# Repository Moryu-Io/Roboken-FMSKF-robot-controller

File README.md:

# Roboken-FMSKF-robot-controller
## 概要
Teensy4.1を使用した新ROBO-剣出場ロボット[Quinque](https://www.robo-one.com/rankings/view/1127)のHW制御統括マイコンFW  
主な役割は以下
- Ethernet経由Micro-ROSで、ロボット全体を統括する上位LinuxPCと情報をやり取りする
- 5軸ロボットアームへの指示、情報収集
- 4輪メカナムホイールモータの速度制御
- 距離センサを用いて床や相手ロボットの検知を簡易的に行う
- 相手ロボット認識用のカメラをPan/Tiltさせるサーボモータを制御

## SW構成(src内)
すべてFreeRTOSのタスクベースでフォルダ分け

| フォルダ名   | 説明                                                                                            |
| ------------ | ----------------------------------------------------------------------------------------------- |
|RobotManager|Ethernet経由Micro-ROSで、上位のLinuxPCと情報をやり取りしながらHW行動を決定するモジュール|
|ArmDrive|5軸ロボットアームの制御を行う。各関節ごとに[ドライバ](https://github.com/Moryu-Io/Bldc_Servo_Driver_Prj)内で位置/トルク制御を行うため、このモジュールでは指示を統括|
|VehicleDrive|4輪メカナムホイールのモータ制御を行う。こちらはDJIのM2006,C610を使用しており、ドライバ内でのトルク制御を行うため、モータの速度制御から上位の指示/制御を統括|
|FloorDetect|競技エリアから落ちないように距離センサで床面をセンシングするモジュール|
|CameraGimbal|カメラをPan/Tiltさせる汎用サーボモータの制御モジュール|
|Logger|Print文をSDカードに保存するためのDebug用モジュール|
|Debug|DebugPrintやRTOSのリソース状況を出力するDebug用モジュール|
|Utility|汎用モジュール。自作の計算処理など|

## 使用ライブラリ
| フォルダ名   | 説明                                                                                            |
| ------------ | ----------------------------------------------------------------------------------------------- |
|[FreeRTOS-Teensy4](https://github.com/juliandesvignes/FreeRTOS-Teensy4)|RTOS|
|[micro_ros_arduino](https://github.com/micro-ROS/micro_ros_arduino)|Micro-ROS Quinque用のカスタムメッセージを含めてビルドしたものを同梱|
|[IcsClass_V210](https://kondo-robot.com/faq/ics-library-a2)|一部使用している近藤科学製サーボモータ制御用|
|[TsyDMASPI](https://github.com/hideakitai/TsyDMASPI)|IMU用SPIだが現状ほぼ未使用|

# 雑多なメモ
## 新規Msgの追加方法
### msgファイルの作成

`micro_ros_arduino\extras\library_generation\extra_packages`直下にmsgフォルダを作る

[公式チュートリアル](https://micro.ros.org/docs/tutorials/advanced/create_new_type/)に従って、.msgファイルの作成とCMakeLists.txtへの登録を行う

ここには記載がないが、package.xml末尾に以下を追加する必要もある
```
  <build_depend>rosidl_default_generators</build_depend>
  <exec_depend>rosidl_default_runtime</exec_depend>
  <member_of_group>rosidl_interface_packages</member_of_group>
```

### micro_ros_arduinoライブラリを作成する
wsl2にて以下のコマンドを発行
```
sudo service docker start

docker pull microros/micro_ros_static_library_builder:foxy
docker run -it --rm -v $(pwd):/project --env MICROROS_LIBRARY_FOLDER=extras microros/micro_ros_static_library_builder:foxy -p teensy4
```
※2022/05/08 wsl2で上記コマンドでdocker使用時に名前解決ができなくなっていた。原因不明。

[このサイト](https://qiita.com/takkeybook/items/37af683bfb1a4eca6aa2)に従って、`/etc/resolv.conf`に記載のDNSサーバーを変更する

### PC側での準備
通信するPC側では同様のmsg定義フォルダを作成
```
colcon build --symlink-install --packages-up-to interfaces
. install/local_setup.bash
ros2 run micro_ros_agent micro_ros_agent udp4 -p 9999
```

### Micro-ROSテスト方法memo
- topic
```
ros2 topic echo /VehicleInfo
```

- service
```
ros2 service call /ProcStatus interfaces/srv/ProcStatus "{id: 1}"
```

## FreeRTOSの初期化修正とFault診断

2026-11-01、初回INITでの再起動を引き起こしていたMSP初期化を修正した。
TeensyduinoのRAMベクタテーブルはslot 0も`unused_interrupt_vector`で埋められる。
従来のFreeRTOSポートは`VTOR → vector[0]`を初期MSPとしていたため、割り込みの
スタック保存がITCM内の`pinMode()`等を上書きしていた。
`prvPortStartFirstTask()`はTeensyのResetHandlerと同じ`_estack`を直接ロードする。
修正後、ユーザーの実機試験で症状が解消したとの報告あり。

RT1062のNVIC優先度も実装に合わせて4bitとし、syscall maskを`0x20`、
kernel priorityを`0xF0`に修正済み。これらの修正は診断defineに依存せず常時有効。
回帰チェックは `python3 test/check_rtos_priorities.py` と、build後の
`python3 test/check_rtos_msp.py`（生成命令で`_estack`のロードを確認）。

再利用するFault診断は `src/Debug/fault_trace.hpp` のdefineで切り替える。
既定はすべて無効。通常ビルドには独自Faultハンドラ・保存RAM・起動診断ログ・
MPU設定変更を含めない。Teensy core標準のFault処理は維持する。

| build flag | 機能 | 既定値 |
| --- | --- | --- |
| `-D ENABLE_FAULT_DIAGNOSTICS=1` | PSP/MSPに対応したFault記録、レジスタ・命令列保存、起動時表示 | `0` |
| `-D ENABLE_ITCM_WRITE_GUARD=1` | 診断有効時、MPUで命令RAMへのCPU書き込みを捕捉 | `0` |

PlatformIOの既存`build_flags`へ必要なflagを追記して使う。ITCM保護には両方を指定する。
ソフトウェアbreakpoint等で実行中のコードを書き換える場合、ITCM保護は無効にする。

診断有効時はUSBシリアル接続後に`[BOOT]`、`[RTOS]`、前回の`[FAULT]` / `CrashReport`を表示する。
接続待ちで起動を止めない。位置特定には`[FAULT] stacked PC`を使う。
core標準のCrashReportはMSP固定なので、FreeRTOSタスクのPCと異なる場合がある。
Fault時のPC周辺64 bytesをFlash内の元コードと比較し、`[CODE]`で出力する。
不正なstackやコード範囲は参照しない。記録はリセットで消えないRAMに識別値・checksum付きで保存する。
既存のカスタムFaultハンドラは置き換えず、標準の報告・自動再起動処理へ戻す。
再起動だけではWatchdogと断定せず、リセット要因とFault種別を確認する。

調査時は実機へ書き込んだ`firmware.elf`とログを対で保存する。再buildするとアドレスが変わる。
記録・範囲チェック・MPU設定保持のホスト検査は `python3 test/check_fault_trace.py`。
GPIO32/34専用のDWT監視、初回INITの段階ログ、旧BASEPRI値の比較検査は撤去した。

micro-ROSは時刻同期に失敗しても購読を維持し、20msの試行を1秒間隔で繰り返す。
同期までは終端イベントをADTの既存16件queueに保持し、同期後に送信する。
接続生成等の長い処理後は周期待ちの基準を更新して、他タスクを圧迫する追い付き実行を避ける。
これらは接続処理の修正として維持する。

## WebUIのマニュアル操作

`Command=12`で専用の手動モードへ入ります。モード切り替え自体は腕の移動やトルクONを行いません。
WebUIは停止指令を先に送り、必要な初期化（4）と構え（1）は別操作にします。
手動では構えの実動作完了後、最初のTimeAngle受信時にPOSITIONING_SEQへ遷移します。
自律開始（2）を送る必要はありません。実行中のTimeAngleと重なる要求は拒否します。

`manual_control/hardware_state`（std_msgs/UInt8）をVehicleInfoと同じ周期で配信します。
0=手動無効、1=手動有効・構え未完了、2=構え完了・打突受付可能、3=打突実行中です。
0（停止・トルクOFF）・2（自律開始）・3（終了）で手動を解除し、1（構え）・4（初期化）では維持します。
走行の床・IMU保護とcmd_velの500 ms watchdogは既存どおりです。

対応するROS側のinterfaces・arm_action_plan・vehicle_action・robot_web_uiと併せて更新してください。
通常の`pio run -e teensy41`でビルドできます。既存のCommandと標準UInt8を使うため、
この変更に伴うmicro_ros_arduinoライブラリの再生成は不要です。書き込みは機体の停止を確認して別途行います。

## FreeRTOS

こちらのリポジトリをベースに、libフォルダに格納
https://github.com/juliandesvignes/FreeRTOS-Teensy4

変更点
* heap3からheap4に
    * heap3はC言語のmallocなどのラッパだが、Teensyduinoではmallocで確保されるのは通常RAM。
    * heap4でucHeapをTCMに配置することで高速性を担保
* 別途configファイルを設定

## アーム実行進捗

`ArmExecutionProgress`（相対topic、reliable）で、`header.stamp`は通知時刻、
`id`はTimeAngle ID、`elapsed_ms`はADTで実際に指令した補間位置、
`status`はRUNNING=0 / COMPLETED=1 / ABORTED=2を送信する。
受信・queue投入時点ではRUNNINGにしない。終端イベントは16件の専用queueに保持し、
RMTタスクから送信する。進行中のsnapshotはcritical sectionで受け渡す。
ArmInfoとProcStatusは引き続き利用できる。

TimeAngleは5軸の点数・各点の時刻が一致する1～32点、時刻は非減少であること。
受信データはADT向けmessageへコピーし、次のROS callbackによる上書きを防ぐ。
不正入力、buffer満杯、POSITIONING_SEQモード外の要求はABORTEDを通知する。
INIT/READYの実動作完了後にMOVE_STARTを送り、その後TimeAngleを送ること。
初期化の途中に送ったMOVE_STARTは実モード遷移を保証せず、早いTimeAngleは拒否される。

RELAX/QUIT_PGは通常message bufferを迂回する停止flagでADT次周期（10ms）に強制OFFし、
実行中・queue済みの軌道をABORTEDにする。pending要求も破棄し、古いMOVE_STARTによる
再始動を防ぐ。停止と同じ制御周期内の再開要求も破棄され得るので、停止確認後に再開する。

### micro-ROS生成物の再生成

同梱版はmicro_ros_arduino 2.0.7-humble。既存のRMW・transport・既存メッセージを維持し、
ArmExecutionProgress専用の生成headerと4個のobjectだけを静的archiveへ追加している。
`extras/library_generation/extra_packages/interfaces/msg/ArmExecutionProgress.msg`が生成元。
以下はローカルにあるDocker builderを使用する（未取得の場合は対応するhumble imageを取得し、
`MICROROS_BUILDER_IMAGE`へ指定）。初回のfirmware workspace作成にはソース取得の通信が必要。

```sh
bash lib/micro_ros_arduino/extras/library_generation/regenerate_arm_progress.sh /tmp/arm-progress-microros
pio run
```

再生成scriptは既存の作業workspaceを再利用する。既存runtime headerとの宣言一致を確認してから
新型objectを追加する。検証使用image ID:
`sha256:bab8476bc71f52332596f2ce15417696ce8ecfbd5a4d3b569c716a5bd34327a4`。
2026-10-09にHumble builderで68 packages生成、PlatformIO teensy41のリンクまで成功。
RMW publisher上限10のうち3枠を使用する。

### メモリ予算と検証範囲

32点×5軸copyによりMSG_REQは32→780 bytes、3件のADT message bufferは
96→2353 bytes（今回はmessage長の管理領域も確保）。共有受信MSG_REQも748 bytes増加する。
終端queueのpayloadは16×12=192 bytesとqueue管理領域。
FreeRTOS heapは36→40 KiBへ増量。設定された9タスクのstack合計は28,160 bytes、
kernel idle/timerのstackは追加1,080 bytes。40 KiBからこれらとADT buffer・終端payloadを引いた
約9 KiBがTCB、他message buffer、queue管理領域等に充てられる（実測空きheapではない）。
RMT stackは既存2304 words、ADTは1024 wordsを維持。

PlatformIOの静的集計: FLASH code 405,988 / data 100,600 bytes、
RAM1 variables 210,020 / code 271,324 / padding 23,588 / local空き19,356 bytes、
RAM2 variables 12,512 / malloc空き511,776 bytes。
実機への書込み・動作試験は未実施で、runtime heap最小値・stack high-waterは未計測。

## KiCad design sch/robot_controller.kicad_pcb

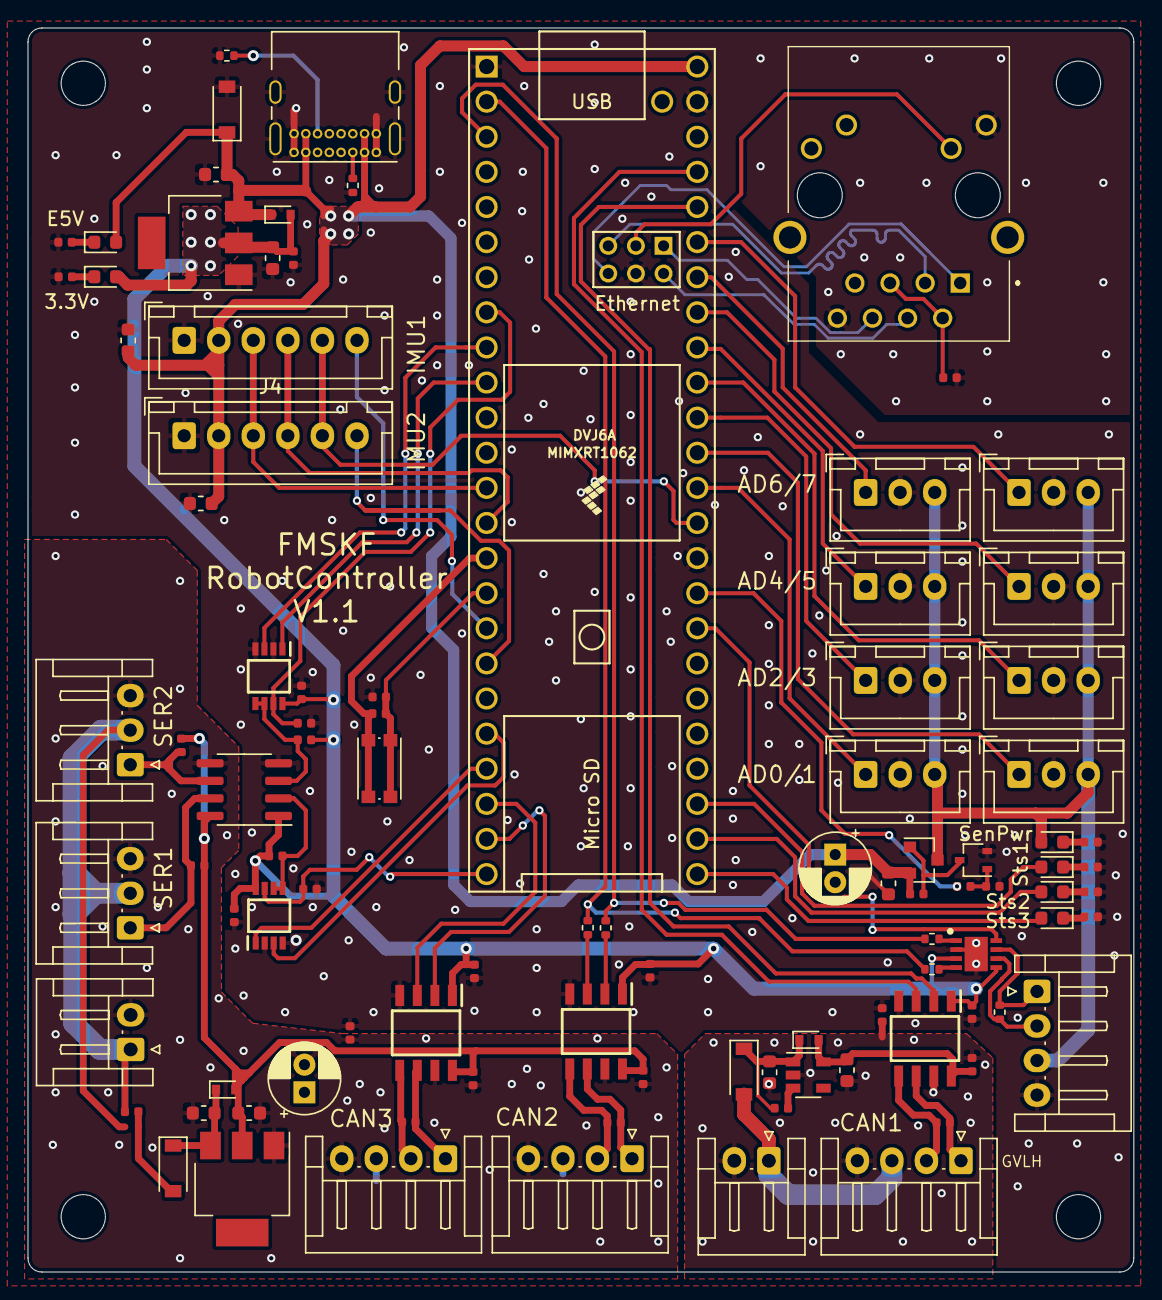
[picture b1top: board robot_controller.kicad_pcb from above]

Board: 2 copper layers, 80.0 x 90.0 mm, 102 parts (0 on the bottom side), 78 nets.

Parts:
C1, C3, C17, C19, C21: 1u; C_0603_1608Metric
C2, C4, C8, C11, C12, C13, C14, C15, C16, C18, C20: 0.1u; C_0402_1005Metric
C5, C6, C7, C22: 10u; C_0603_1608Metric
C24, C25: 47u; CP_Radial_D5.0mm_P2.00mm
D1, D7, D11: PMEG6010CEGWJ; D_SOD-123
D2, D4, D6, D13, D14, D15: LED; LED_0603_1608Metric
D5, D9, D12: RB5105SM-40T; D_SOD-523
H1, H2, H3, H4: MountingHole; MountingHole_3.2mm_M3
IC1, IC2, IC5: ISO1044BDR; SOIC127P600X175-8N
IC3, IC4: 74LVC2G125DP,125; SOP65P400X110-8N
IC6: TLT9251VLEXUMA1; SON65P300X300X110-9N
J1: USB_C_Receptacle_USB2.0; USB_C_Receptacle_GCT_USB4085
J2, J4: Conn_01x06; JST_XH_B6B-XH-A_1x06_P2.50mm_Vertical
J3: RJ45_LED; J1B1211CCD
J5, J6, J7, J8, J9, J10, J11, J12: Conn_01x03; JST_XH_B3B-XH-A_1x03_P2.50mm_Vertical
J13, J15, J17, J18: Conn_01x04; JST_EH_S4B-EH_1x04_P2.50mm_Horizontal
J16, J20: Conn_01x02; JST_EH_S2B-EH_1x02_P2.50mm_Horizontal
J19, J21: Conn_01x03; JST_EH_S3B-EH_1x03_P2.50mm_Horizontal
Q2: 2SC4116; SOT-323_SC-70
Q4: IRLML6402; SOT-23
R1, R10, R12, R14, R23, R24, R27, R28, R31, R36, R37: 10k; R_0402_1005Metric
R2, R5: 5.1k; R_0402_1005Metric
R3, R16, R22, R38, R39, R40: 1k; R_0402_1005Metric
R4, R6, R8, R9, R25, R26, R33: 0; R_0402_1005Metric
R7, R29, R30, R35: 60; R_0402_1005Metric
SW1: SW_SPST; SW_Push_1P1T_NO_CK_KMR2
U1: Teensy4.1; Teensy41simple_onlyeth
U2: AZ1117-3.3; SOT-223
U3: ISO1540; SOIC-8_3.9x4.9mm_P1.27mm
U4: NCP718xSN500; SOT-23-5
U5: LD1117S50TR_SOT223; SOT-223-3_TabPin2

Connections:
+3.3VP: C7.1, C8.1, C11.1, C12.1, C13.1, C14.1, C18.1, D5.2, D6.2, IC1.1, IC2.1, IC3.8, IC4.8, IC5.1, IC6.3, IC6.5, R27.1, R28.1, U2.2, U3.1
+3V3: C4.1, SW1.1, U1.15, U1.46
+5VL: C1.1, C3.1, C5.1, C6.1, C24.1, D1.1, D2.2, D5.1, J1.A4, J1.A9, J1.B4, J1.B9, J2.2, J4.2, Q4.2, R12.1, U1.48, U2.3
/5V_P1: C15.1, C19.1, D9.2, IC5.8, U4.5
/5V_P3: C16.1, C20.1, C22.2, D12.2, IC1.8, IC2.8, R36.1, R37.1, U3.8, U5.2
/CAN1_H: IC5.6, J15.1, R29.1
/CAN1_L: IC5.5, J15.2, R29.2
/CAN1_RX: IC5.3, U1.45
/CAN1_TX: IC5.2, U1.44
/CAN2_H: IC1.6, J18.1, R35.1
/CAN2_L: IC1.5, J18.2, R35.2
/CAN2_RX: R6.1, R9.1, U1.2
/CAN2_TX: R4.1, R8.1, U1.3
/CAN3_H: IC2.6, J17.1, R30.1
/CAN3_L: IC2.5, J17.2, R30.2
/CAN3_RX: IC2.3, U1.22
/CAN3_TX: IC2.2, U1.23
/ETH_LED: J3.10, U1.61
/ETH_RX+: J3.6, U1.60
/ETH_RX-: J3.4, U1.65
/ETH_TX+: J3.1, U1.63
/ETH_TX-: J3.3, U1.62
/GND_P1: C15.2, C17.2, C19.2, IC5.7, J15.4, J16.2, R25.2, U4.2
/GND_P3: C16.2, C20.2, C21.1, C22.1, C25.2, IC1.7, IC2.7, J17.4, J18.4, J19.3, J20.2, J21.3, R26.2, U3.5, U5.1
/IMU_SPI_CS1: J2.6, U1.17
/IMU_SPI_CS2: J4.6, U1.18
/IMU_SPI_MISO: J2.4, J4.4, U1.14
/IMU_SPI_MOSI: J2.3, J4.3, U1.13
/IMU_SPI_SCK: J2.5, J4.5, U1.35
/SERIAL2_EN: IC4.7, R24.1, U1.8
/SERIAL2_RX: IC4.3, U1.9
/SERIAL2_TX: IC4.1, U1.10
/SERIAL7_EN: IC3.7, R23.1, U1.24
/SERIAL7_RX: IC3.3, U1.20
/SERIAL7_TX: IC3.1, U1.21
/TTL_SERIAL1: J19.1, R37.2, U3.7
/TTL_SERIAL2: J21.1, R36.2, U3.6
/USER_SWITCH: C4.2, R1.2, SW1.2, U1.16
/VCC_P1: D7.2, J15.3, J16.1
/VCC_P3: C25.1, J17.3, J18.3, J19.2, J20.1, J21.2, R33.1
/WALLTOF_CAN_EN: IC6.8, U1.32
/WALL_AD0: J5.1, U1.36
/WALL_AD1: J6.1, U1.37
/WALL_AD2: J7.1, U1.38
/WALL_AD3: J8.1, U1.39
/WALL_AD4: J9.1, U1.40
/WALL_AD5: J10.1, U1.41
/WALL_AD6: J11.1, U1.42
/WALL_AD7: J12.1, U1.43
/WALL_PWR: R10.1, U1.33
/WALL_VCC: D4.2, J5.3, J6.3, J7.3, J8.3, J9.3, J10.3, J11.3, J12.3, J13.3, Q4.3
GND: C1.2, C2.2, C3.2, C5.2, C6.2, C7.2, C8.2, C11.2, C12.2, C13.2, C14.2, C18.2, C24.2, D1.2, IC1.4, IC2.4, IC3.2, IC3.4, IC4.2, IC4.4, IC5.4, IC6.2, IC6.9, J1.A1, J1.A12, J1.B1, J1.B12, J1.S1, J2.1, J3.8, J3.9, J4.1, J5.2, J6.2, J7.2, J8.2, J9.2, J10.2, J11.2, J12.2, J13.4, Q2.2, R1.1, R2.2, R3.2, R5.1, R14.2, R16.2, R22.2, R23.2, R24.2, R25.1, R26.1, R38.2, R39.2, R40.2, U1.1, U1.34, U1.47, U1.64, U2.1, U3.4
unnamed: C2.1, J3.2, J3.5
unnamed: C17.1, D7.1, D9.1, R31.1, U4.1
unnamed: C21.2, D11.1, D12.1, U5.3
unnamed: D2.1, R3.1
unnamed: D4.1, R16.1
unnamed: D6.1, R22.1
unnamed: D11.2, R33.2
unnamed: D13.1, R38.1
unnamed: D13.2, U1.25
unnamed: D14.1, R39.1
unnamed: D14.2, U1.26
unnamed: D15.1, R40.1
unnamed: D15.2, U1.27
unnamed: IC1.2, R8.2
unnamed: IC1.3, R9.2
unnamed: IC3.5, IC3.6, R27.2, U3.2
unnamed: IC4.5, IC4.6, R28.2, U3.3
unnamed: IC6.1, R4.2
unnamed: IC6.4, R6.2
unnamed: IC6.6, J13.2, R7.2
unnamed: IC6.7, J13.1, R7.1
unnamed: J1.A5, R2.1
unnamed: J1.B5, R5.2
unnamed: Q2.1, R10.2, R14.1
unnamed: Q2.3, Q4.1, R12.2
unnamed: R31.2, U4.3

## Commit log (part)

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2022-04-23 add : base libraries
2022-04-24 feat : Imu Com (Test)
2022-05-01 fix : sch
2022-05-02 feat : disable LED0 ( for imu spi sck)
2022-05-02 feat : utility of register modification
2022-05-02 feat : disable D-cache
2022-05-02 style : update clang-format
2022-05-02 feat : enable adc&dma for floor sensors
2022-05-02 feat : enable a kondo servo for the yaw0 joint
2022-05-02 feat : max stack size of tasks
2022-05-04 feat : motor CAN com
2022-05-08 feat : enable a FreeRTOS run time counter
2022-05-08 feat : micro-ros interfaces
2022-05-08 add : micro-ros-arduino lib (custom)
2022-05-15 fix : CAN rx msg filter masks
2022-05-15 feat : get status of vehicle motors
2022-05-15 style : VDT arrange
2022-05-15 feat : vehicle move dir command
2022-05-15 feat : global config
2022-05-15 style : Micro-ros setup function
2022-06-12 feat : setup CAN3 for a gimbal motor of pitch
2022-06-12 feat : setup CAN2 for my bldc servos
2022-06-15 feat : Arm Initialize mode
2022-06-15 feat : debug task
2022-06-15 feat : ADT message
2022-06-16 feat : positioning (non test)
2022-06-18 fix : my servo current lim unit
2022-06-18 fix : ics servo connection flag
2022-06-18 fix : CAN mailbox status print disable
2022-06-18 feat : add debug print
2022-06-18 feat : Micro-Ros connection wait
2022-06-18 debug
2022-06-18 fix : NULL ptr exception (TimeAngleMsg)
2022-06-19 feat : add debug info
2022-06-19 fix : move cmd status
2022-06-19 fix : joint message order
2022-06-19 fix : variable length message of ROS
2022-06-20 feat : TimeAngle seq (no confirm)
2022-06-22 fix : time angle command
2022-06-22 feat : posseq mode
2022-06-22 feat : VDT motor vel control
2022-06-27 feat : Floor detection temp
2022-06-27 fix : time angle seq data array
2022-06-27 feat : vehicle velocity control
2022-06-27 fix : Jetson IP address
2022-06-28 feat : differential gear joint 1
2022-06-28 feat : arm servo init default function
2022-06-29 feat : [ADT] pos seq debug func
2022-06-29 fix : my servo CAN config
2022-06-29 feat : servo can config fix
2022-06-29 fix : ADT init & reset func
2022-06-29 param : adt
2022-06-29 fix : gimbal servo protocol fix
2022-06-29 fix : differential gear calc fix
2022-06-29 fix : ADT other update
2022-06-30 feat : [ADT] add only init pos move
2022-07-02 feat : enable commandif subscribe
2022-07-02 feat : floor and wall detect function
2022-07-02 style : ADT text format
2022-07-02 feat : use Jetson local network
2022-07-02 feat : gimbal servo pos control by trq con
2022-07-02 feat : motor dir changable (only my servo)
2022-07-04 debug off
2022-07-04 add ics servo stretch
2022-07-04 fix : adt init mode
2022-07-04 buffer increase
2022-08-12 update : sch
2022-08-12 fix : vehicle speed control
2022-08-12 fix : delete no use include
2022-08-12 refactor : move rtos debug info to debug task
2022-08-13 feat : add base of SD Logger Task
2022-09-18 feat : mg4005 servo motor
2022-09-18 feat : mg servo config
2022-09-18 feat : mg gimbal pos and move req coexistance
2022-09-19 feat : prevent time-angle cmd overlap
2022-09-23 add local address
2022-09-23 fix : microros setting
2022-09-23 disable arm debug printf
2022-09-23 fix : case of time angle id 0
2022-09-23 add serial monitor speed config
2022-09-23 feat : SD card logging
2022-09-23 add doc
2022-10-02 disable ADT debug print
2022-10-08 feat : process load measurement
2022-10-08 temp : trajectory generator temp script
2022-10-16 feat : velocity control (const jerk)
2022-10-18 feat : vehicle debug control by key inputs
2022-10-23 feat : vehicle motor control logger
2022-10-23 feat : vehicle doukaku
2022-10-23 feat : MG4005 for pitch1
2022-10-29 camera gimbal enable
2022-10-29 camera gimbal enable add
2022-10-29 vehicle speed limit
2022-11-02 param : camera gimbal angle
2022-11-02 feat : camera task config
2022-11-02 temp : mg servo pos con by torque instr
2022-11-02 update microros library
2022-11-03 fix : timeout of eth read func
2022-11-05 fix : arm drive pos seq bug
2022-11-05 microros reconnection
2022-11-05 microros com update
2022-11-05 add proc load enum
2022-11-05 mg motor torque control
2022-11-06 mg servo pos con rivival
2022-11-06 camera init pitch angle update
2022-11-06 uros ping duration update
2022-11-08 fix : vehicle rotate direction
2022-11-11 arm drive bug fix
2022-11-12 mg servo stability update
2022-11-12 fix : arm control bug
2022-11-12 update arm init pos
2022-11-12 arm log visualizer
2022-11-12 update fdt threthold params
2022-11-13 update floor detect
2022-11-13 update parameter
2022-11-13 fix adt initialize seq
2022-11-16 camera params update
2022-11-18 camera gimbal initialize update
2022-11-18 floor detection threshold update
2022-11-18 params update
2023-09-18 update microros to humble
2023-10-01 adt posseq improve
2023-10-04 board update v2
2023-10-14 enable driving time of vehicle
2023-10-15 in sch updating
2023-10-15 mecanum continuous order
2023-10-16 double buffer of mecanum command
2023-10-28 vdtask cont order
2023-10-29 vehicle cont order ok
2023-11-18 vehicle params update
2023-11-18 update floor detect type and get vehicle speed
2023-11-19 vehicle cmd abort addon (fault status)
2023-11-19 fix vehicle order abort judgement
2023-11-19 VDT fix gain rot
2023-11-19 VDT parameter update
2024-08-18 sch update
2024-09-07 feat : swicth of floor detection
2024-09-07 feat : camera gimbal yaw
2024-11-16 adjust floor detect params
2024-11-16 add camera yaw control
2024-11-16 camera gimbal merge miss
2024-11-16 fix cam yaw
2024-11-16 cam angle order
2024-11-16 fix libmicroros a
2024-11-16 floor sensor config on
2024-11-16 off debug print fdt
2024-11-17 fix floor sensor judge method and params
2025-06-21 feat : wt901ttl
2025-06-22 feat : add odm topic
2025-06-22 fix : odom topic
2025-06-23 temporary adjust direction quat
2025-06-24 feat : double buffer for imu
2025-06-25 feat : odometry
2025-06-25 fix : gear ratio inv
2025-08-30 add cmd vel if
2025-09-14 add vel field to vehicle info msg
2025-09-14 update microros
2025-09-14 fix bug
2025-09-21 fix cmdvel topic name
2025-11-08 fix floor sensor flag
2025-11-08 fix some
2025-11-14 fix parameter
2025-11-15 add floor ignore switch
2025-11-15 fix cmd num
2025-11-15 temporary camera task off
2026-02-22 Revert "temporary camera task off"
    This reverts commit c090d6b953e579bf34f4e5df4c758a91819cbdc7.
